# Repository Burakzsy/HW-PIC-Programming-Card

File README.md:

## PIC-Programlama-Kartı
ICSP tekniği ile pic programlama

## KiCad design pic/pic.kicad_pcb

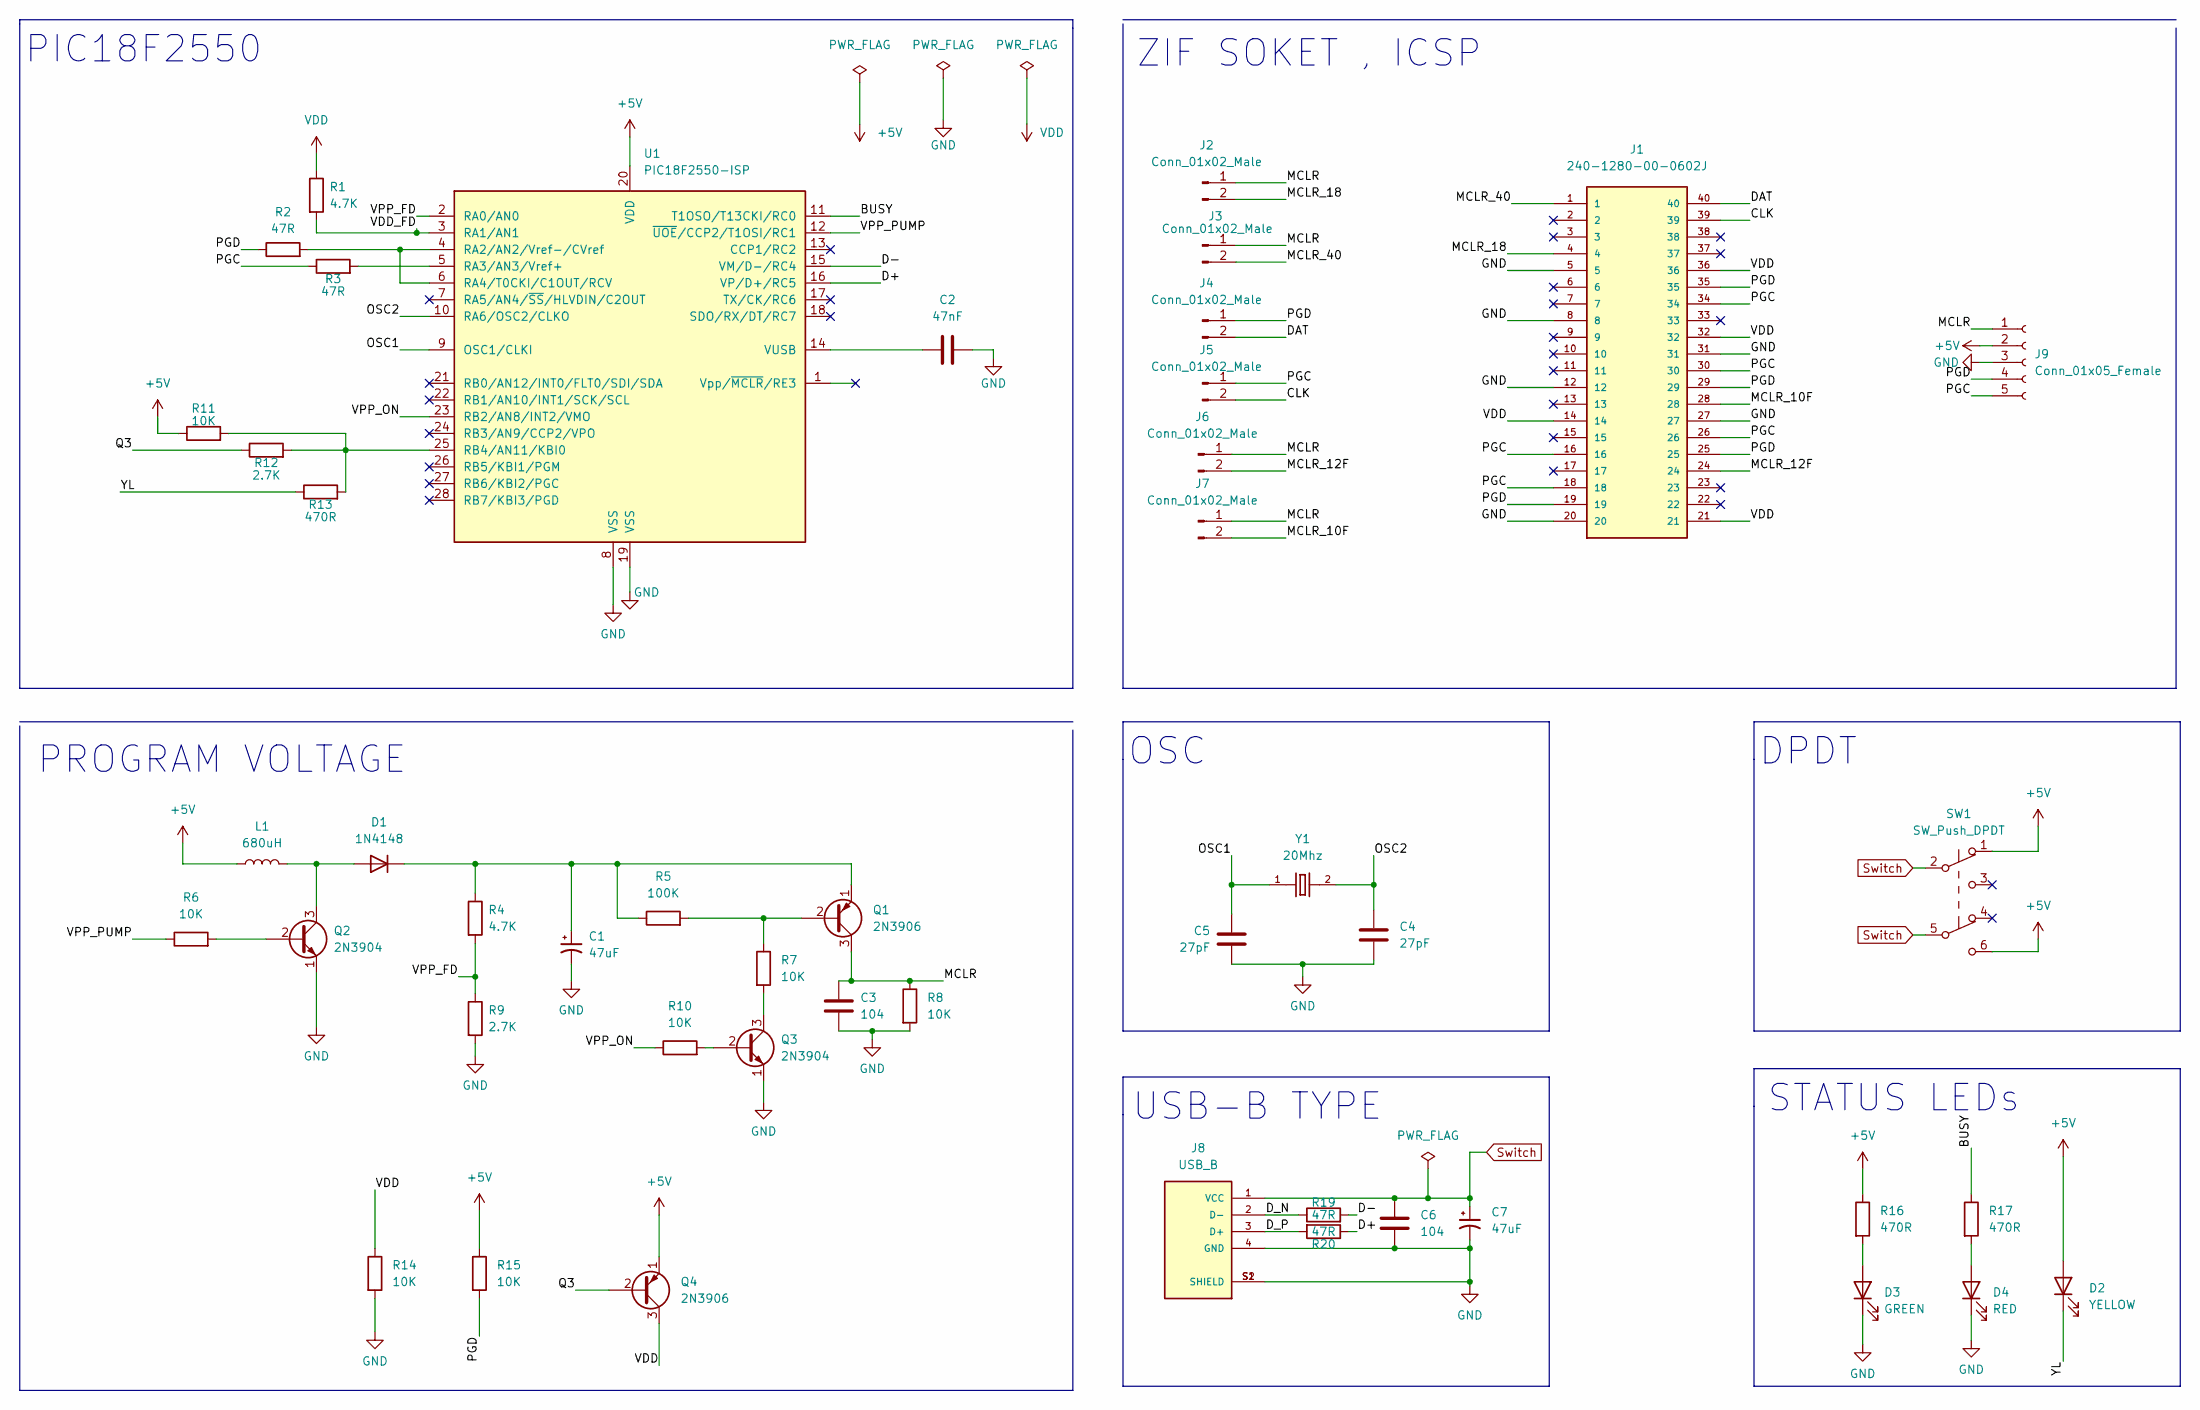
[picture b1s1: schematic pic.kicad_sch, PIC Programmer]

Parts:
C1, C7: 47uF; CP_Radial_D7.5mm_P2.50mm
C2: 47nF; C_Disc_D5.0mm_W2.5mm_P2.50mm
C3, C6: 104; C_Disc_D6.0mm_W2.5mm_P5.00mm
C4, C5: 27pF; C_Disc_D5.0mm_W2.5mm_P2.50mm
D1: 1N4148; D_DO-35_SOD27_P7.62mm_Horizontal
D2: YELLOW; LED_D5.0mm
D3: GREEN; LED_D5.0mm
D4: RED; LED_D5.0mm
J1: 240-1280-00-0602J; 3M_240-1280-00-0602J; PARTREV E
J2, J3, J4, J5, J6, J7: Conn_01x02_Male; PinHeader_1x02_P2.54mm_Vertical
J8: USB_B; SAMTEC_USB-B-S-X-X-TH; PARTREV Q
J9: Conn_01x05_Female; PinSocket_1x05_P2.54mm_Vertical
L1: 680uH; L_Axial_L7.0mm_D3.3mm_P10.16mm_Horizontal_Fastron_MICC
Q1, Q4: 2N3906; TO-92_Inline
Q2, Q3: 2N3904; TO-92_Inline
R1, R4: 4.7K; R_Axial_DIN0207_L6.3mm_D2.5mm_P7.62mm_Horizontal
R2, R3, R19, R20: 47R; R_Axial_DIN0207_L6.3mm_D2.5mm_P7.62mm_Horizontal
R5: 100K; R_Axial_DIN0207_L6.3mm_D2.5mm_P7.62mm_Horizontal
R6, R7, R8, R10, R11, R14, R15: 10K; R_Axial_DIN0207_L6.3mm_D2.5mm_P7.62mm_Horizontal
R9, R12: 2.7K; R_Axial_DIN0207_L6.3mm_D2.5mm_P7.62mm_Horizontal
R13, R16, R17: 470R; R_Axial_DIN0207_L6.3mm_D2.5mm_P7.62mm_Horizontal
SW1: SW_Push_DPDT; SW_TL2230EEF100
U1: PIC18F2550-ISP; DIP-28_W7.62mm
Y1: 20Mhz; XTAL_ECS-200-S-4X

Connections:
+5V: D2.2 (A), J9.2, L1.1, Q4.1 (E), R11.1, R15.1, R16.1, SW1.1 (A), SW1.6 (C), U1.20 (VDD)
/BUSY: R17.1, U1.11 (T1OSO/T13CKI/RC0)
/CLK: J1.39, J5.2
/D+: R20.1, U1.16 (VP/D+/RC5)
/D-: R19.2, U1.15 (VM/D-/RC4)
/DAT: J1.40, J4.2
/D_N: J8.2 (D-), R19.1
/D_P: J8.3 (D+), R20.2
/MCLR: C3.2, J2.1, J3.1, J6.1, J7.1, J9.1, Q1.3 (C), R8.1
/MCLR_10F: J1.28, J7.2
/MCLR_12F: J1.24, J6.2
/MCLR_18: J1.4, J2.2
/MCLR_40: J1.1, J3.2
/OSC1: C5.2, U1.9 (OSC1/CLKI), Y1.1
/OSC2: C4.2, U1.10 (RA6/OSC2/CLKO), Y1.2
/PGC: J1.16, J1.18, J1.26, J1.30, J1.34, J5.1, J9.5, R3.1
/PGD: J1.19, J1.25, J1.29, J1.35, J4.1, J9.4, R2.1, R15.2
/Q3: Q4.2 (B), R12.1
/VDD_FD: R1.2, U1.3 (RA1/AN1)
/VPP_FD: R4.2, R9.1, U1.2 (RA0/AN0)
/VPP_ON: R10.1, U1.23 (RB2/AN8/INT2/VMO)
/VPP_PUMP: R6.1, U1.12 (~UOE/CCP2/T1OSI/RC1)
/YL: D2.1 (K), R13.1
GND: C1.2, C2.2, C3.1, C4.1, C5.1, C6.1, C7.2, D3.1 (K), D4.1 (K), J1.5, J1.8, J1.12, J1.20, J1.27, J1.31, J8.4 (GND), J8.S1 (SHIELD), J8.S2 (SHIELD), J9.3, Q2.1 (E), Q3.1 (E), R8.2, R9.2, R14.2, U1.8 (VSS), U1.19 (VSS)
unnamed: C1.1, D1.1 (K), Q1.1 (E), R4.1, R5.1
unnamed: C2.1, U1.14 (VUSB)
unnamed: D1.2 (A), L1.2, Q2.3 (C)
unnamed: D3.2 (A), R16.2
unnamed: D4.2 (A), R17.2
unnamed: Q1.2 (B), R5.2, R7.1
unnamed: Q2.2 (B), R6.2
unnamed: Q3.2 (B), R10.2
unnamed: Q3.3 (C), R7.2
unnamed: R2.2, U1.4 (RA2/AN2/Vref-/CVref), U1.6 (RA4/T0CKI/C1OUT/RCV)
unnamed: R3.2, U1.5 (RA3/AN3/Vref+)
unnamed: R11.2, R12.2, R13.2, U1.25 (RB4/AN11/KBI0)
Switch: C6.2, C7.1, J8.1 (VCC), SW1.2 (B), SW1.5 (B)
VDD: J1.14, J1.21, J1.32, J1.36, Q4.3 (C), R1.1, R14.1

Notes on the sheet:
PIC18F2550
OSC
DPDT
USB-B TYPE
ZIF SOKET , ICSP
PROGRAM VOLTAGE
STATUS LEDs

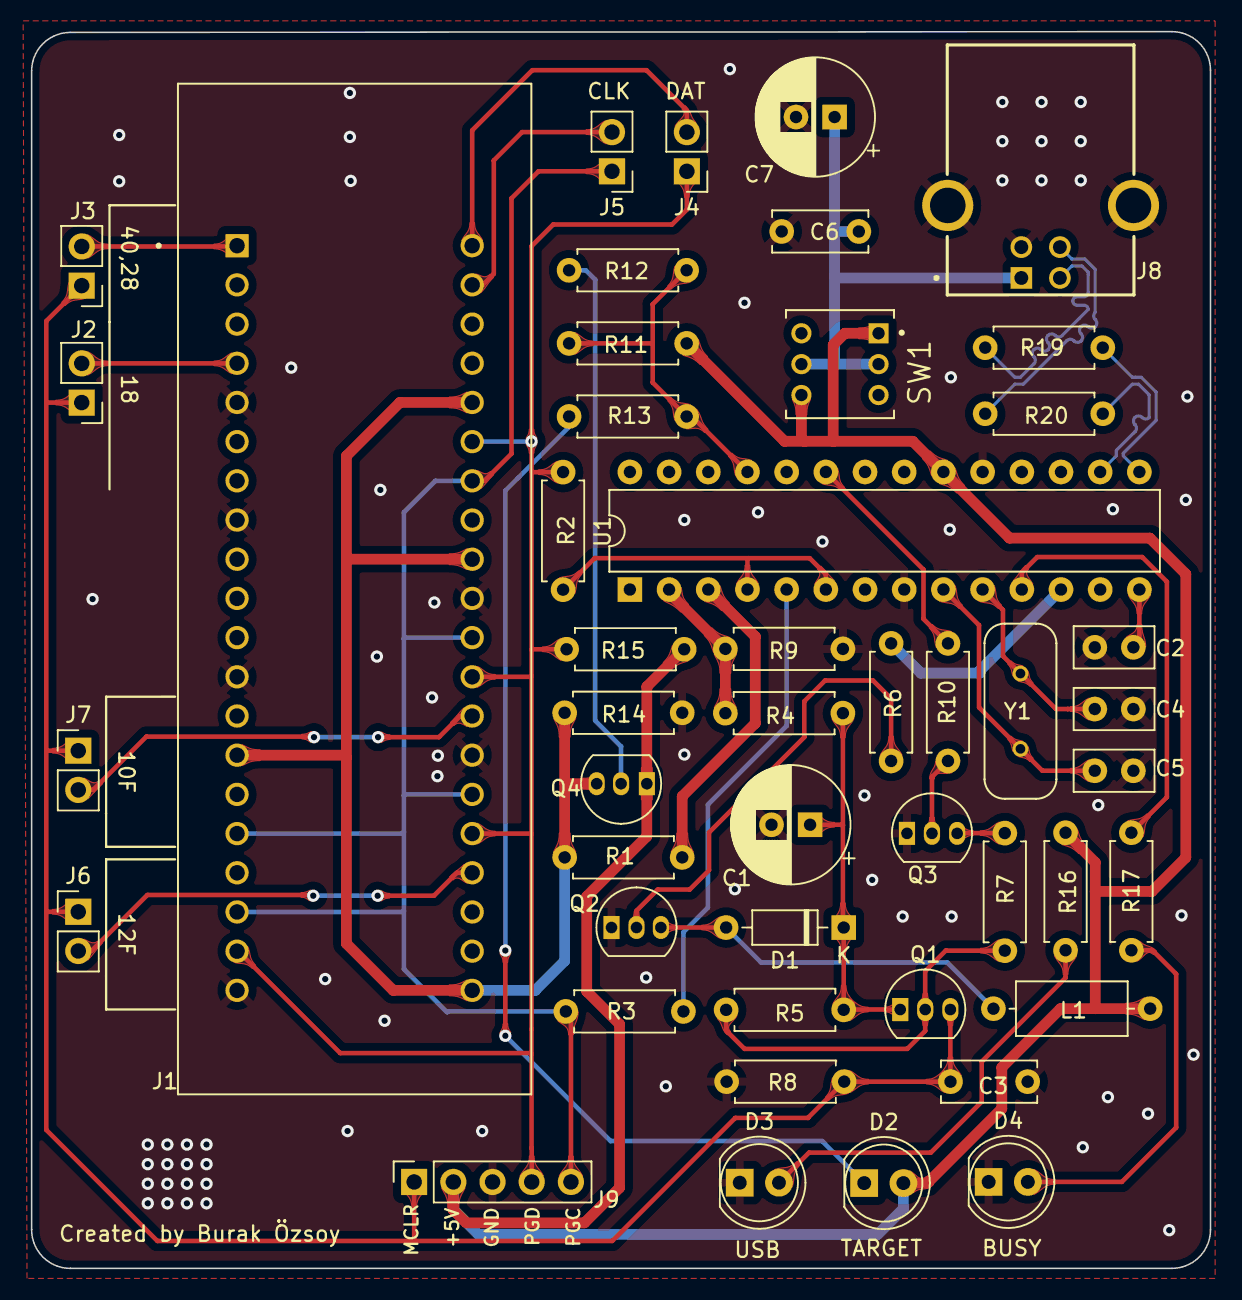
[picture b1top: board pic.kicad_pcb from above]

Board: 2 copper layers, 76.4 x 80.1 mm, 47 parts (0 on the bottom side), 38 nets.

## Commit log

2023-04-28 PIC Programlayıcı
    ICSP tekniği ile pic programlama kartı
2024-05-09 Deploy to GitHub pages
